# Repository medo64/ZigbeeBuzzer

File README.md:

# Zigbee Buzzer

Zigbee notification device allowing for multiple notifications using sound.

## Usage

When device is first used, button should be pressed to wake up the device. It
will immediately enter the pairing mode and remain in it for 3 minutes. If
device is not paired within 3 minutes, it will enter deep sleep again.

LED will be normally off. If LED is blinking slowly (about 1 Hz), device is
waiting to be paired. Fast double blinks will indicate communication error.

If device is paired, a short button press will cause device to immediately report
its state upon releasing.

Long press of 3-5s will make device enter pairing mode. LED will turn on once
3s interval starts and turn off after 5th second has passed.

Long press of 30-35 seconds will reset unit to factory settings and place it
into deep sleep until the next button press.

Long press while LED is off, will be ignored.

## Components

Each notification sound is exposed as a button.

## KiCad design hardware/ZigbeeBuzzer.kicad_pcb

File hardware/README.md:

## Zigbee Buzzer Hardware

### Parts

|  # | Part                                             | RefDes  |
|---:|--------------------------------------------------|---------|
|  1 | C 10nF X7R 16V (0805)                            | C1      |
|  1 | C 10uF X5R 16V (0805)                            | C2      |
|  1 | D Schottky [CUS08F30,H3F] (SOD323)               | D1      |
|  1 | DS LED (0805)                                    | DS1     |
|  1 | LS Passive Buzzer                                | LS1     |
|  1 | Q NPN 100mA 20V [BC846B,235] (SOT23-3)           | Q1      |
|  1 | R 470 0.125W (0805)                              | R1      |
|  3 | R 1K 0.125W (0805)                               | R2-R4   |
|  1 | R 2.2K 0.125W (0805)                             | R5      |
|  2 | R 100K 0.125W (0805)                             | R6-R7   |
|  1 | S Tactile 4.0x4.0x1.5mm                          | S1      |
|  1 | U Wireless [Xiao ESP32-C6]                       | U1      |

#### Board Size

|       |      Dimensions | Area    | Thickness |
|-------|-----------------|---------|-----------|
| PCB   |  26.0 x 21.0 mm | 0.9 in² |    0.8 mm |

#### Flyback diode

Diode is needed only if inductive diode is used (e.g. vibration motor). This is
used for testing purposes only at this time.

#### Battery

Battery can be optionally attached. This is currently used only for testing.

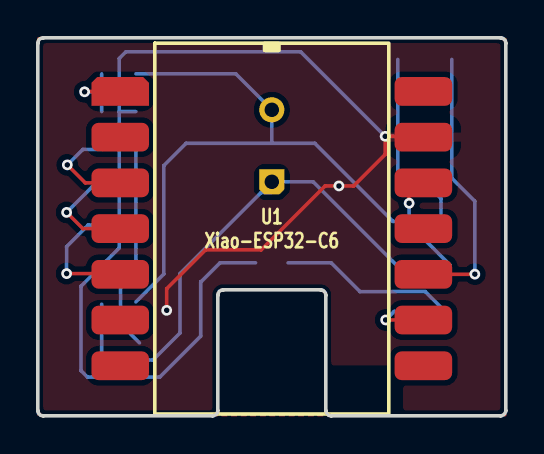
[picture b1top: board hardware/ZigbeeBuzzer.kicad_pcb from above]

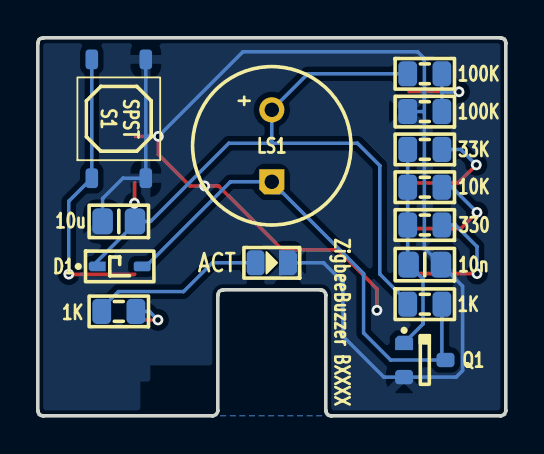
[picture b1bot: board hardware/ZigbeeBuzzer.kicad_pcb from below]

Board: 2 copper layers, 26.0 x 21.0 mm, 15 parts (14 on the bottom side), 11 nets.

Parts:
C1: 10n; C (0805)
C2: 10u; C (0805)
D1: CUS08F30; D Schottky (SOD323)
DS1: ACT; DS (0805)
LS1: LS Buzzer (D9.5-H5.5)
Q1: NPN; Q Transistor NPN (SOT23-3)
R1: 330; R (0805)
R2, R3: 1K; R (0805)
R4: 10K; R (0805)
R5: 33K; R (0805)
R7, R8: 100K; R (0805)
S1: SPST; S Tactile SPST-NO 12V 50mA 4.0x4.0x1.5mm (SMD-4)
U1: Xiao-ESP32-C6; U Wireless [Xiao ESP32C6] (SMD-14)

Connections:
3V3: C2.1, D1.1, LS1.2, R2.1, R7.1, U1.12
ADC: R7.2, R8.1, U1.1
BASE: C1.2, Q1.1, R1.2, R4.2, R5.2
BEEPER: D1.2, LS1.1, Q1.3, R2.2
BUTTON: S1.1, U1.10
GND: C1.1, C2.2, DS1.1, Q1.2, R8.2, S1.2, U1.13
LED: DS1.2, R3.2
OUT_LED: R3.1, U1.9
PWM1: R5.1, U1.3
PWM2: R4.1, U1.4
PWM3: R1.1, U1.5

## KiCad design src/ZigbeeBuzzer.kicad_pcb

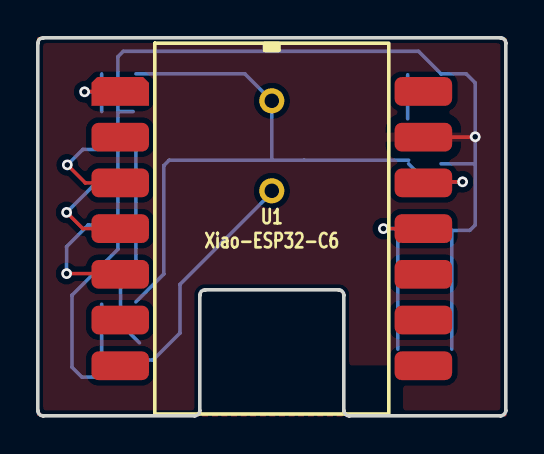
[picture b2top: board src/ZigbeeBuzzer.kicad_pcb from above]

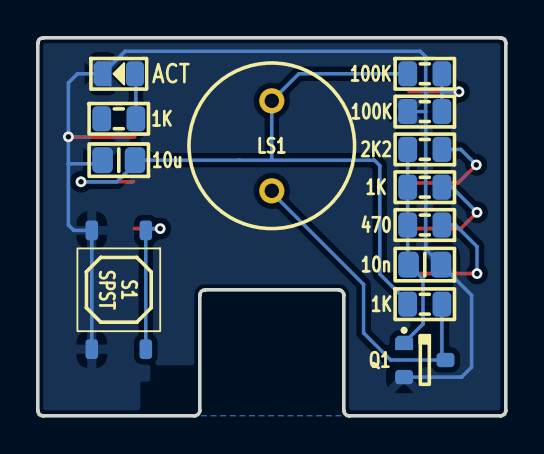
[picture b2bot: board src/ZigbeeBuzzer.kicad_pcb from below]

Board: 2 copper layers, 26.0 x 21.0 mm, 14 parts (13 on the bottom side), 10 nets.

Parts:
C1: 10n; C (0805)
C2: 10u; C (0805)
DS1: ACT; DS (0805)
LS1: LS Buzzer (D9.5-H5.5)
Q1: NPN; Q Transistor NPN (SOT23-3)
R1: 470; R (0805)
R2, R3, R4: 1K; R (0805)
R5: 2K2; R (0805)
R7, R8: 100K; R (0805)
S1: SPST; S Tactile SPST-NO 12V 50mA 4.0x4.0x1.5mm (SMD-4)
U1: Xiao-ESP32-C6; U Wireless [Xiao ESP32C6] (SMD-14)

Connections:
3V3: C2.1, LS1.1, R3.1, R7.1, U1.12
ADC: R7.2, R8.1, U1.1
BASE: C1.2, Q1.1, R1.2, R2.2, R5.2
BEEPER: LS1.2, Q1.3, R3.2
BUTTON: S1.1, U1.11
GND: C1.1, C2.2, DS1.1, Q1.2, R8.2, S1.2, U1.13
LED: DS1.2, R4.2
PWM1: R5.1, U1.3
PWM2: R2.1, U1.4
PWM3: R1.1, U1.5
